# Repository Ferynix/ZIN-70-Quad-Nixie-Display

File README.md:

# ZIN-70 Quad Nixie Display
 
### Important Notes

This is a four tube display built using Millclock ZIN-70 Nixie Tubes. This can be used to drive a clock, or just as a numeric display.

Please note that if you decide to use this display as a clock, it does not include a colon.

Current iteration: Version 2

### Components and Requirements

Supply:
* Any* 12V 500mA (or better) supply. DC 5.5mm Male Plug

Mechanical and Connectors:
* 1x Same Sky `PJ-063AH` DC 5.5mm Female Connector 
* 1x C&K Switches `DP62J12S202HQ` DPDT Slide Switch (Power Switch)
* 2x Same Sky `TS04-66-85-BK-100-SMT` SPST Button (Hour and Minute buttons)
* 2x Keystone Elec. `1291-66 ` 9V Battery connector

Tubes:
* 4x Millclock `ZIN-70` Nixie Tubes (Z5680M Pinout) - 170V ~5mA each
* 1x NE-2 5mm "Daytime" Indicator (I used a yellow phosphor Mercury/Argon tube)
* 1x NE-2 5mm "Nighttime" Indicator (I used a blue phosphor Mercury/Argon Tube)

Passives:
* 4x 6.8kR 1206(in) SMD Current-Limiting Power Resistors (Nixie Tubes)
    - (or 5K if you wish to run at a bit higher current)
* 8x 1kR 1206(in) SMD Current-Limiting Signal Resistors (Outputs)
* 4x 200kR 1206(in) SMD Current-Limiting Power Resistors (Indicator Swapper)
* 2x 100nF 1206(in) SMD Decoupling Capacitors
* 2x 1uF 1206(in) SMD Filter Capacitors
* 2x 10k 1206(in) SMD Filter Resistors

HV Boost Supply:
* 1x Omnixie `NCH8200HV` (12V to 170V 30mA)
    - Custom footprint. Only compatible with NCH8200V.

Driver:
* 1x Murata `OKI-78SR-5/1.5-W36-C` 12-5V DC-DC Converter 
    - Custom footprint for this device. Swap or remove as required
* 1x Murata `OKI-78SR-12/1.0-W36-C` 18-12V DC-DC Converter 
    - Custom footprint for this device. Swap or remove as required
* 1x WaveShare `RP2040-Tiny` devboard 
    - Custom footprint. Please swap for your driver. Only compatible with 23-pin 2.54mm pitch RP2040 tinies.
    - Buy directly from waveshare if you want to avoid incompatibility.

Registers and Other:
* 2x Microchip Tech. `HV5122` PQFP-44 32bit HV Registers (220V 100mA Drains)
    - Custom symbol/package configured. 
* 4x TO-92 NPN Transistor (any with E B C pinout) such as 2N2222
    - Faster transistors better!
* 2x >0.5A Through-hole Diode - 1N400X series intended, equivalent works.

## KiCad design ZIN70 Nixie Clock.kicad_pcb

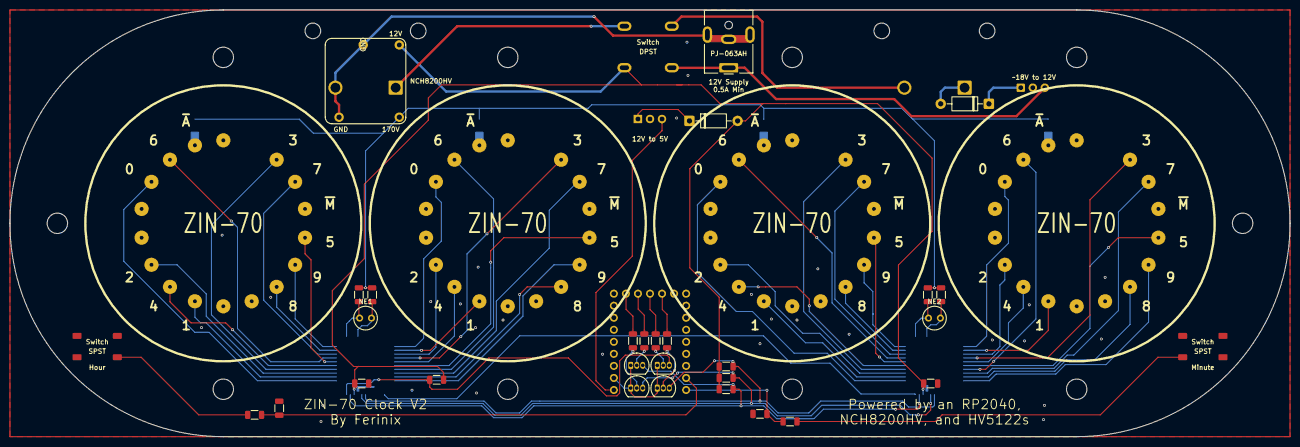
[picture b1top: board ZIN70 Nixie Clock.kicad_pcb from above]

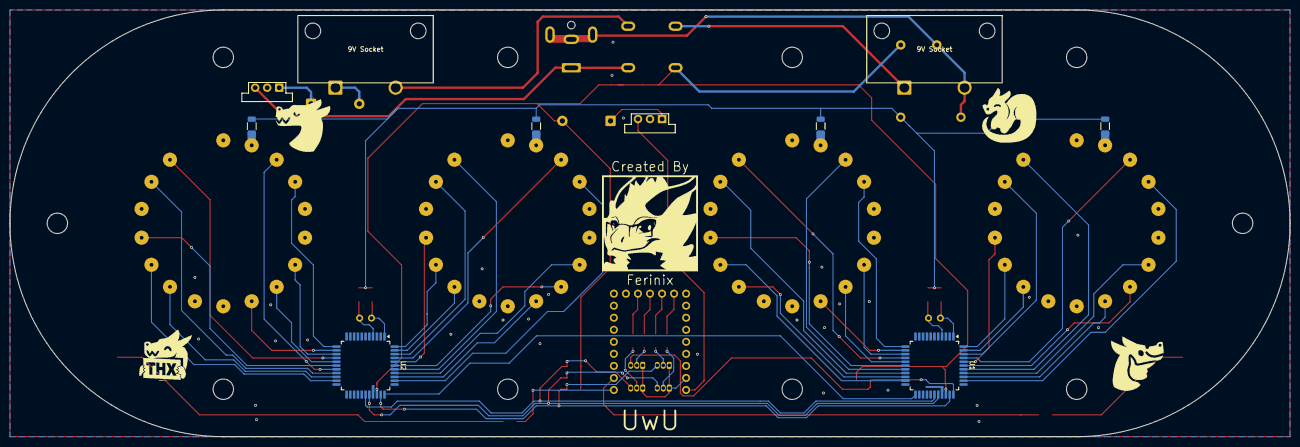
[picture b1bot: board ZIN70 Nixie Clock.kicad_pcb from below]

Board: 2 copper layers, 270.0 x 90.0 mm, 45 parts (10 on the bottom side), 63 nets.

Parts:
9V Socket, 9V Socket#2: 9V Socket Slim
C1, C2: 100nF; C_1206_3216Metric
C_DB: 1uF; C_1206_3216Metric
C_DB#2: 1uF; C_1206_3216Metric
D1, D2: 1N4007; D_DO-41_SOD81_P10.16mm_Horizontal
NCH8200HV: NCH8200HV Through-Hole
NE1, NE2: NE-2; NE-2_5mm
NIX1, NIX2, NIX3, NIX4: ZIN-70; ZIN-70 Z5680M Pinout
PJ-063AH: BarrelJack_CUI_PJ-063AH_Horizontal
Q1, Q2, Q3, Q4: PN2222A; TO-92_Inline
R1, R2, R3, R4: 6.8K; R_1206_3216Metric
R5, R6, R7, R8: 200K; R_1206_3216Metric
R9, R10, R11, R12, R13, R14, R15, R16: 1K; R_1206_3216Metric
R_DB: 1K; R_1206_3216Metric
R_DB#2: 1K; R_1206_3216Metric
Switch: TS04-66-85-BK-100-SMT SPST Button
Switch#2: DP62J12S202HQ DPDT Slide Switch
Switch#3: TS04-66-85-BK-100-SMT SPST Button
U1, U2: HV5122; PQFP-44_10x10mm_P0.8mm
U3, U4: OKI-78SR-3.3_1.5-W36-C; Converter_DCDC_Murata_OKI-78SR_Vertical

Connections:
+12V: C1.1, C2.1, D1.2 (A), NCH8200HV.1, PJ-063AH.1, R9.1, R10.1, R11.1, R12.1, Switch#2.1, Switch#2.2, U1.31 (VDD), U2.31 (VDD), U4.3 (OUT)
+18V: 9V Socket.2, 9V Socket#2.1, 9V Socket#2.2, D2.2 (A), Switch#2.3, Switch#2.4
+170V: NCH8200HV.2, R1.1, R2.1, R3.1, R4.1, R5.2, R6.2, R7.2, R8.2
GND: 9V Socket.1, C1.2, C2.2, C_DB.2, C_DB#2.2, NCH8200HV.3, NCH8200HV.4, PJ-063AH.2, PJ-063AH.MP, Q1.1 (E), Q2.1 (E), Q3.1 (E), Q4.1 (E), Switch.1, Switch#3.3, U1.30 (GND), U2.30 (GND), U3.2 (GND), U4.2 (GND)
unnamed: D1.1 (K), U3.1 (IN)
unnamed: D2.1 (K), U4.1 (IN)
unnamed: NIX1.4 (0), U1.35 (HV1)
unnamed: NIX1.9 (1), U1.36 (HV2)
unnamed: NIX1.7 (2), U1.37 (HV3)
unnamed: NIX1.17 (3), U1.38 (HV4)
unnamed: NIX1.8 (4), U1.39 (HV5)
unnamed: NIX1.14 (5), U1.40 (HV6)
unnamed: NIX1.3 (6), U1.41 (HV7)
unnamed: NIX1.16 (7), U1.42 (HV8)
unnamed: NIX1.12 (8), U1.43 (HV9)
unnamed: NIX1.13 (9), U1.44 (HV10)
unnamed: NIX1.2 (~A), R1.2
unnamed: NIX2.4 (0), U1.12 (HV22)
unnamed: NIX2.9 (1), U1.13 (HV23)
unnamed: NIX2.7 (2), U1.14 (HV24)
unnamed: NIX2.17 (3), U1.15 (HV25)
unnamed: NIX2.8 (4), U1.16 (HV26)
unnamed: NIX2.14 (5), U1.17 (HV27)
unnamed: NIX2.3 (6), U1.18 (HV28)
unnamed: NIX2.16 (7), U1.19 (HV29)
unnamed: NIX2.12 (8), U1.20 (HV30)
unnamed: NIX2.13 (9), U1.21 (HV31)
unnamed: NIX2.2 (~A), R2.2
unnamed: NIX3.4 (0), U2.35 (HV1)
unnamed: NIX3.9 (1), U2.36 (HV2)
unnamed: NIX3.7 (2), U2.37 (HV3)
unnamed: NIX3.17 (3), U2.38 (HV4)
unnamed: NIX3.8 (4), U2.39 (HV5)
unnamed: NIX3.14 (5), U2.40 (HV6)
unnamed: NIX3.3 (6), U2.41 (HV7)
unnamed: NIX3.16 (7), U2.42 (HV8)
unnamed: NIX3.12 (8), U2.43 (HV9)
unnamed: NIX3.13 (9), U2.44 (HV10)
unnamed: NIX3.2 (~A), R3.2
unnamed: NIX4.4 (0), U2.12 (HV22)
unnamed: NIX4.9 (1), U2.13 (HV23)
unnamed: NIX4.7 (2), U2.14 (HV24)
unnamed: NIX4.17 (3), U2.15 (HV25)
unnamed: NIX4.8 (4), U2.16 (HV26)
unnamed: NIX4.14 (5), U2.17 (HV27)
unnamed: NIX4.3 (6), U2.18 (HV28)
unnamed: NIX4.16 (7), U2.19 (HV29)
unnamed: NIX4.12 (8), U2.20 (HV30)
unnamed: NIX4.13 (9), U2.21 (HV31)
unnamed: NIX4.2 (~A), R4.2
unnamed: Q1.2 (B), R13.1
unnamed: Q1.3 (C), R12.2, U1.33 (DIN)
unnamed: Q2.2 (B), R14.1
unnamed: Q2.3 (C), R11.2, U1.28 (~OE), U2.28 (~OE)
unnamed: Q3.2 (B), R15.1
unnamed: Q3.3 (C), R10.2, U1.29 (CLK), U2.29 (CLK)
unnamed: Q4.2 (B), R16.1
unnamed: Q4.3 (C), R9.2, U1.32 (STR), U2.32 (STR)
unnamed: U1.23 (DATAOUT), U2.33 (DIN)
unnamed: R5.1, U1.1 (HV11)
unnamed: R6.1, U1.4 (HV14)
unnamed: R7.1, U2.1 (HV11)
unnamed: R8.1, U2.4 (HV14)

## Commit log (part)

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2026-03-18 Fix all issues, replace some components, simplify / improve design
2026-03-18 Minor adjustments
2026-03-30 Adjustments I forgot to save
2026-04-13 Just committing
